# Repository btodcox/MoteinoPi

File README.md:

MoteinoPi
=========

Interface board that allows a Moteino to be connected to a Raspberry Pi vi serial and SPI.

## What's a Moteino? ##
For information about the Moteino, visit [www.lowpowerlab.com](http://www.lowpowerlab.com) to learn more.

## What the heck is this project? ##
See the MoteinoPi thread in the lowpowerlab forum [here](http://lowpowerlab.com/forum/index.php/topic,240.0.html).

## Want to order a copy of this PCB? 
See the link in the MoteinoPi thread in the lowpowerlab forum!

## License
[Creative Commons BY-SA](https://creativecommons.org/licenses/by-sa/3.0/us/)

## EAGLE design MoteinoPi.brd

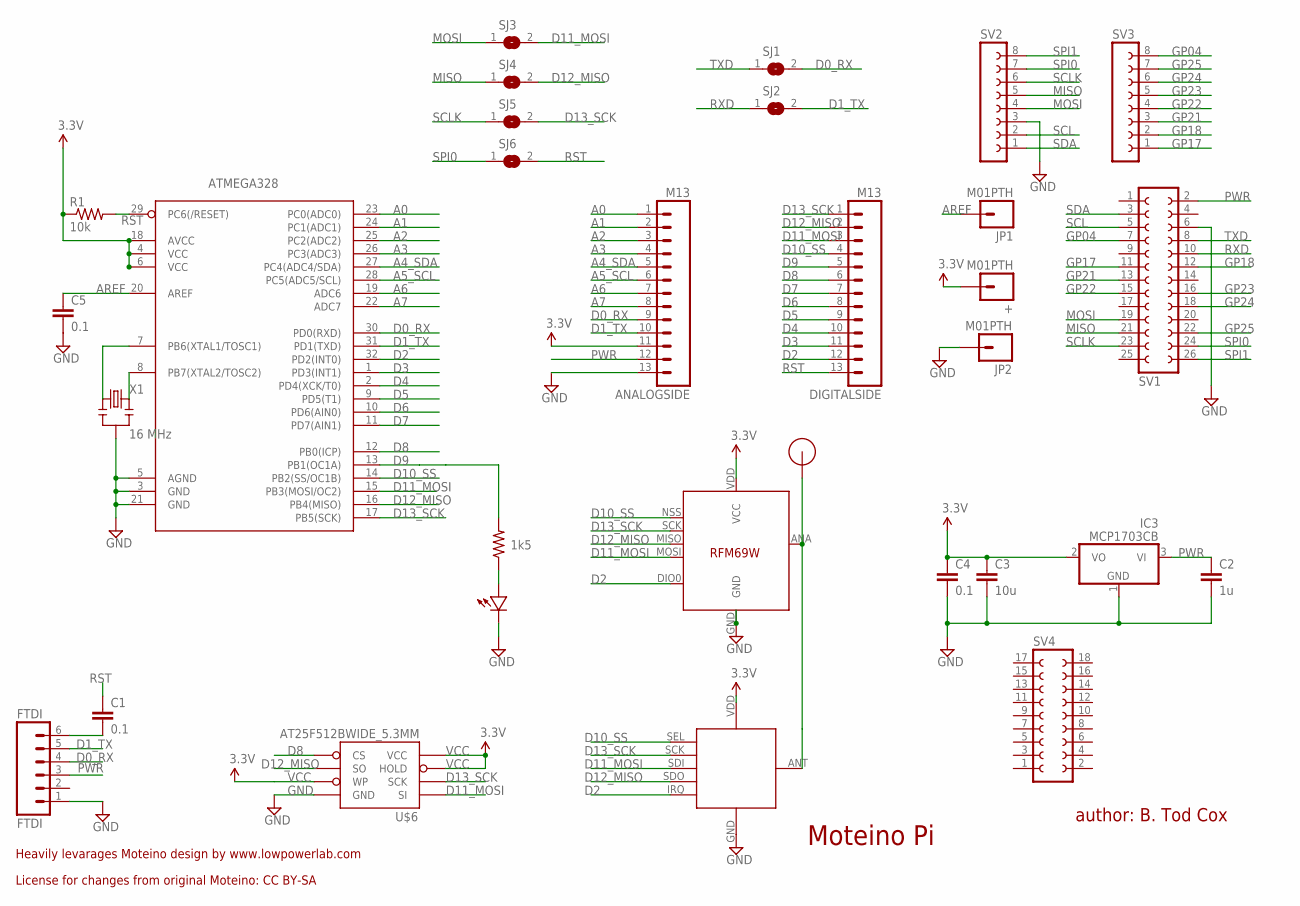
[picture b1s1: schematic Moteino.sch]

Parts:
+: M01PTH; 1X01
ANALOGSIDE: M13; 1X13
ATMEGA328: ATMega-328; TQFP32-08
C1, C4, C5: 0.1; 0603-CAP
C2: 1u; 0603-CAP
C3: 10u; 0805-CAP
DIGITALSIDE: M13; 1X13
FTDI: FTDI; 1X06
IC3: MCP1703CB; SOT23
JP1, JP2: M01PTH; 1X01
R1: 10k; 0603-RES
R2: 1k5; 0603-RES
RFM12B: RFM12B_MINPADS; RFM12B-MINPADS
SJ1, SJ2, SJ3, SJ4, SJ5, SJ6: SJ
SV1: FE13-2
SV2, SV3: FE08-1; FE08
SV4: FE09-2
U$1: RFM12B_ANTENNA; RFM12B-ANTENNA
U$2: LED0603; 0603-LED
U$5: RFM69; RFM69W-MINPADS
U$6: AT25F512BWIDE_5.3MM; SO08WIDE
X1: 16 MHz; RESONATOR-SMD

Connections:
A0: ANALOGSIDE.1, ATMEGA328.23 (PC0(ADC0))
A1: ANALOGSIDE.2, ATMEGA328.24 (PC1(ADC1))
A2: ANALOGSIDE.3, ATMEGA328.25 (PC2(ADC2))
A3: ANALOGSIDE.4, ATMEGA328.26 (PC3(ADC3))
A4_SDA: ANALOGSIDE.5, ATMEGA328.27 (PC4(ADC4/SDA))
A5_SCL: ANALOGSIDE.6, ATMEGA328.28 (PC5(ADC5/SCL))
A6: ANALOGSIDE.7, ATMEGA328.19 (ADC6)
A7: ANALOGSIDE.8, ATMEGA328.22 (ADC7)
AREF: ATMEGA328.20 (AREF), C5.1, JP1.1
D0_RX: ANALOGSIDE.9, ATMEGA328.30 (PD0(RXD)), FTDI.4, SJ1.2
D1_TX: ANALOGSIDE.10, ATMEGA328.31 (PD1(TXD)), FTDI.5, SJ2.2
D2: ATMEGA328.32 (PD2(INT0)), DIGITALSIDE.12, RFM12B.IRQ, U$5.DIO0
D3: ATMEGA328.1 (PD3(INT1)), DIGITALSIDE.11
D4: ATMEGA328.2 (PD4(XCK/T0)), DIGITALSIDE.10
D5: ATMEGA328.9 (PD5(T1)), DIGITALSIDE.9
D6: ATMEGA328.10 (PD6(AIN0)), DIGITALSIDE.8
D7: ATMEGA328.11 (PD7(AIN1)), DIGITALSIDE.7
D8: ATMEGA328.12 (PB0(ICP)), DIGITALSIDE.6, U$6.1 (CS)
D9: ATMEGA328.13 (PB1(OC1A)), DIGITALSIDE.5, R2.2
D10_SS: ATMEGA328.14 (PB2(SS/OC1B)), DIGITALSIDE.4, RFM12B.SEL, U$5.NSS (SEL)
D11_MOSI: ATMEGA328.15 (PB3(MOSI/OC2)), DIGITALSIDE.3, RFM12B.SDI (SDI/MOSI), SJ3.2, U$5.MOSI, U$6.5 (SI)
D12_MISO: ATMEGA328.16 (PB4(MISO)), DIGITALSIDE.2, RFM12B.SDO (SDO/MISO), SJ4.2, U$5.MISO, U$6.2 (SO)
D13_SCK: ATMEGA328.17 (PB5(SCK)), DIGITALSIDE.1, RFM12B.SCK, SJ5.2, U$5.SCK, U$6.6 (SCK)
GND: ANALOGSIDE.13, ATMEGA328.3 (GND), ATMEGA328.5 (AGND), ATMEGA328.21 (GND), C2.2, C3.2, C4.2, C5.2, FTDI.1, IC3.1 (GND), JP2.1, RFM12B.GND, SV1.6, SV2.3, U$2.MINUS, U$5.GND, U$6.4 (GND), X1.2
GP04: SV1.7, SV3.8
GP17: SV1.11, SV3.1
GP18: SV1.12, SV3.2
GP21: SV1.13, SV3.3
GP22: SV1.15, SV3.4
GP23: SV1.16, SV3.5
GP24: SV1.18, SV3.6
GP25: SV1.22, SV3.7
MISO: SJ4.1, SV1.21, SV2.5
MOSI: SJ3.1, SV1.19, SV2.4
unnamed: ATMEGA328.7 (PB6(XTAL1/TOSC1)), X1.1
unnamed: R2.1, U$2.PLUS
unnamed: RFM12B.ANT, U$1.P$1, U$5.ANA (ANT)
unnamed: C1.2, FTDI.6
unnamed: ATMEGA328.8 (PB7(XTAL2/TOSC2)), X1.3
PWR: ANALOGSIDE.12, C2.1, FTDI.3, IC3.3 (VI), SV1.2
RST: ATMEGA328.29 (PC6(/RESET)), C1.1, DIGITALSIDE.13, R1.2, SJ6.2
RXD: SJ2.1, SV1.10
SCL: SV1.5, SV2.2
SCLK: SJ5.1, SV1.23, SV2.6
SDA: SV1.3, SV2.1
SPI0: SJ6.1, SV1.24, SV2.7
SPI1: SV1.26, SV2.8
TXD: SJ1.1, SV1.8
VCC: +.1, ANALOGSIDE.11, ATMEGA328.4 (VCC), ATMEGA328.6 (VCC), ATMEGA328.18 (AVCC), C3.1, C4.1, IC3.2 (VO), R1.1, RFM12B.VDD, U$5.VDD (VCC), U$6.3 (WP), U$6.7 (HOLD), U$6.8 (VCC)

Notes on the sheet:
Moteino Pi
author: B. Tod Cox
Heavily levarages Moteino design by www.lowpowerlab.com
License for changes from original Moteino: CC BY-SA

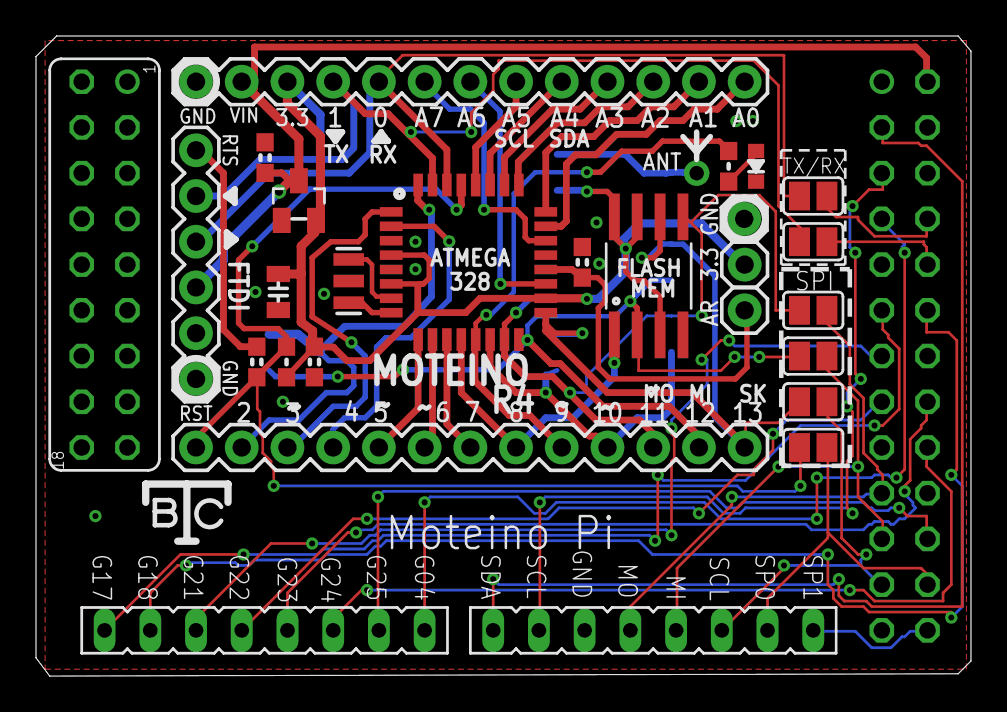
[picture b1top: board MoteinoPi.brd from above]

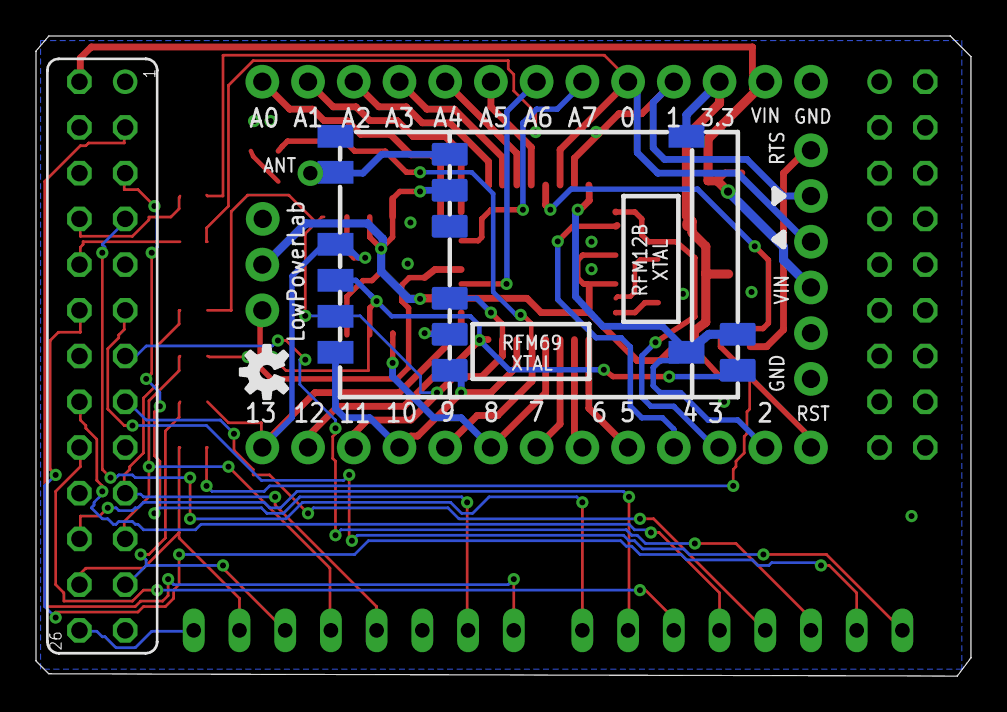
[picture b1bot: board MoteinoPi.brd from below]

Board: 2 copper layers, 51.9 x 35.6 mm, 32 parts (4 on the bottom side), 49 nets.

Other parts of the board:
U$3: OSHW-LOGO-S

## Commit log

2014-04-11 Add readme
2014-04-11 added link to CC license
2014-04-11 renaming files to better names

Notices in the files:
parts and their libraries:
SparkFun-Connectors: Licensing: CC v3.0 Share-Alike You are welcome to use this library for commercial purposes.
